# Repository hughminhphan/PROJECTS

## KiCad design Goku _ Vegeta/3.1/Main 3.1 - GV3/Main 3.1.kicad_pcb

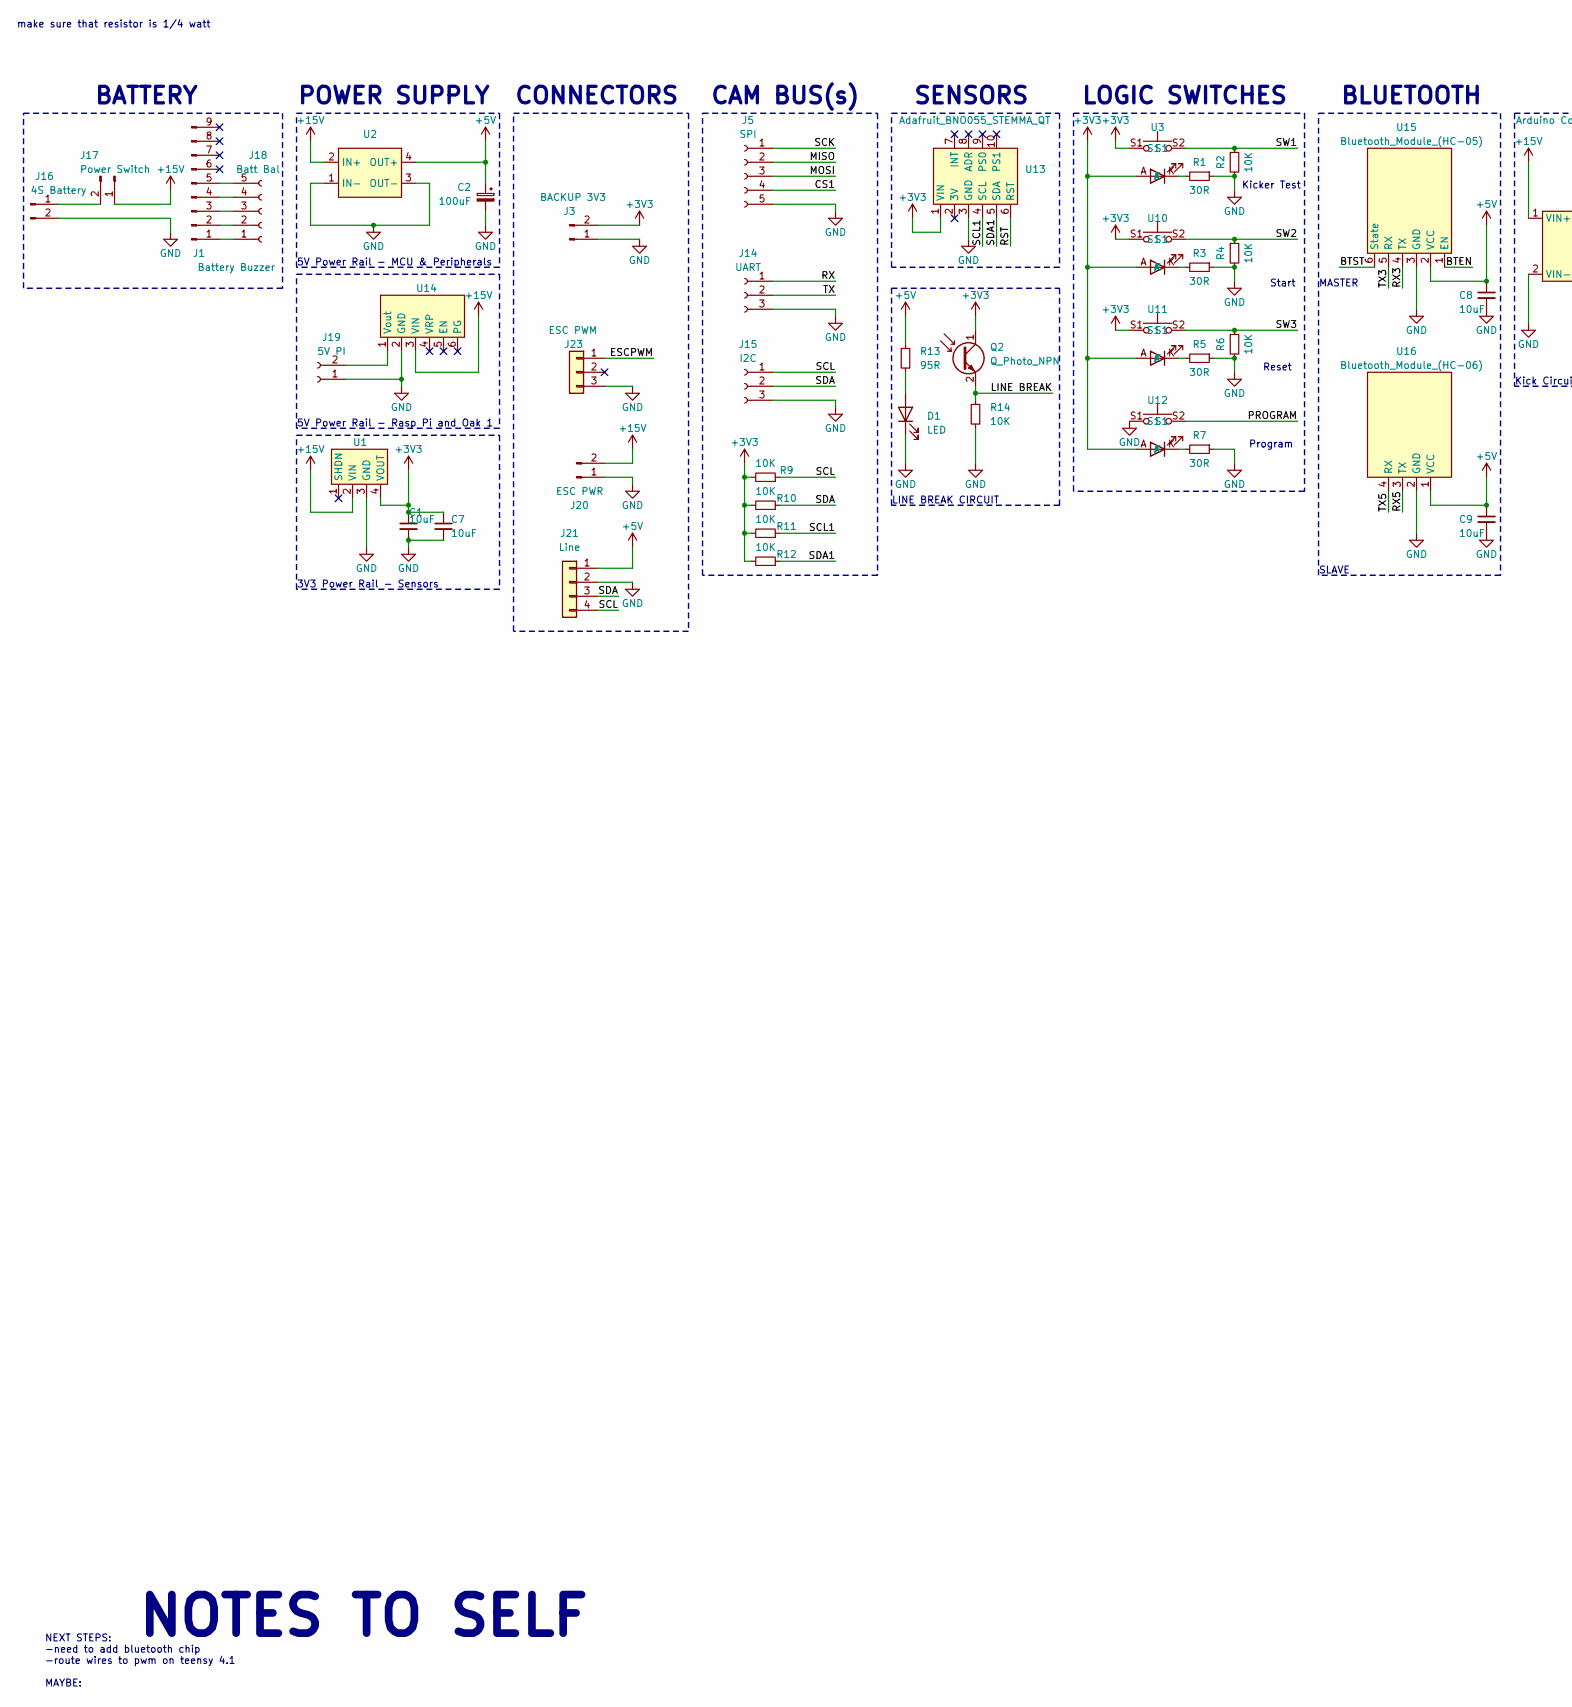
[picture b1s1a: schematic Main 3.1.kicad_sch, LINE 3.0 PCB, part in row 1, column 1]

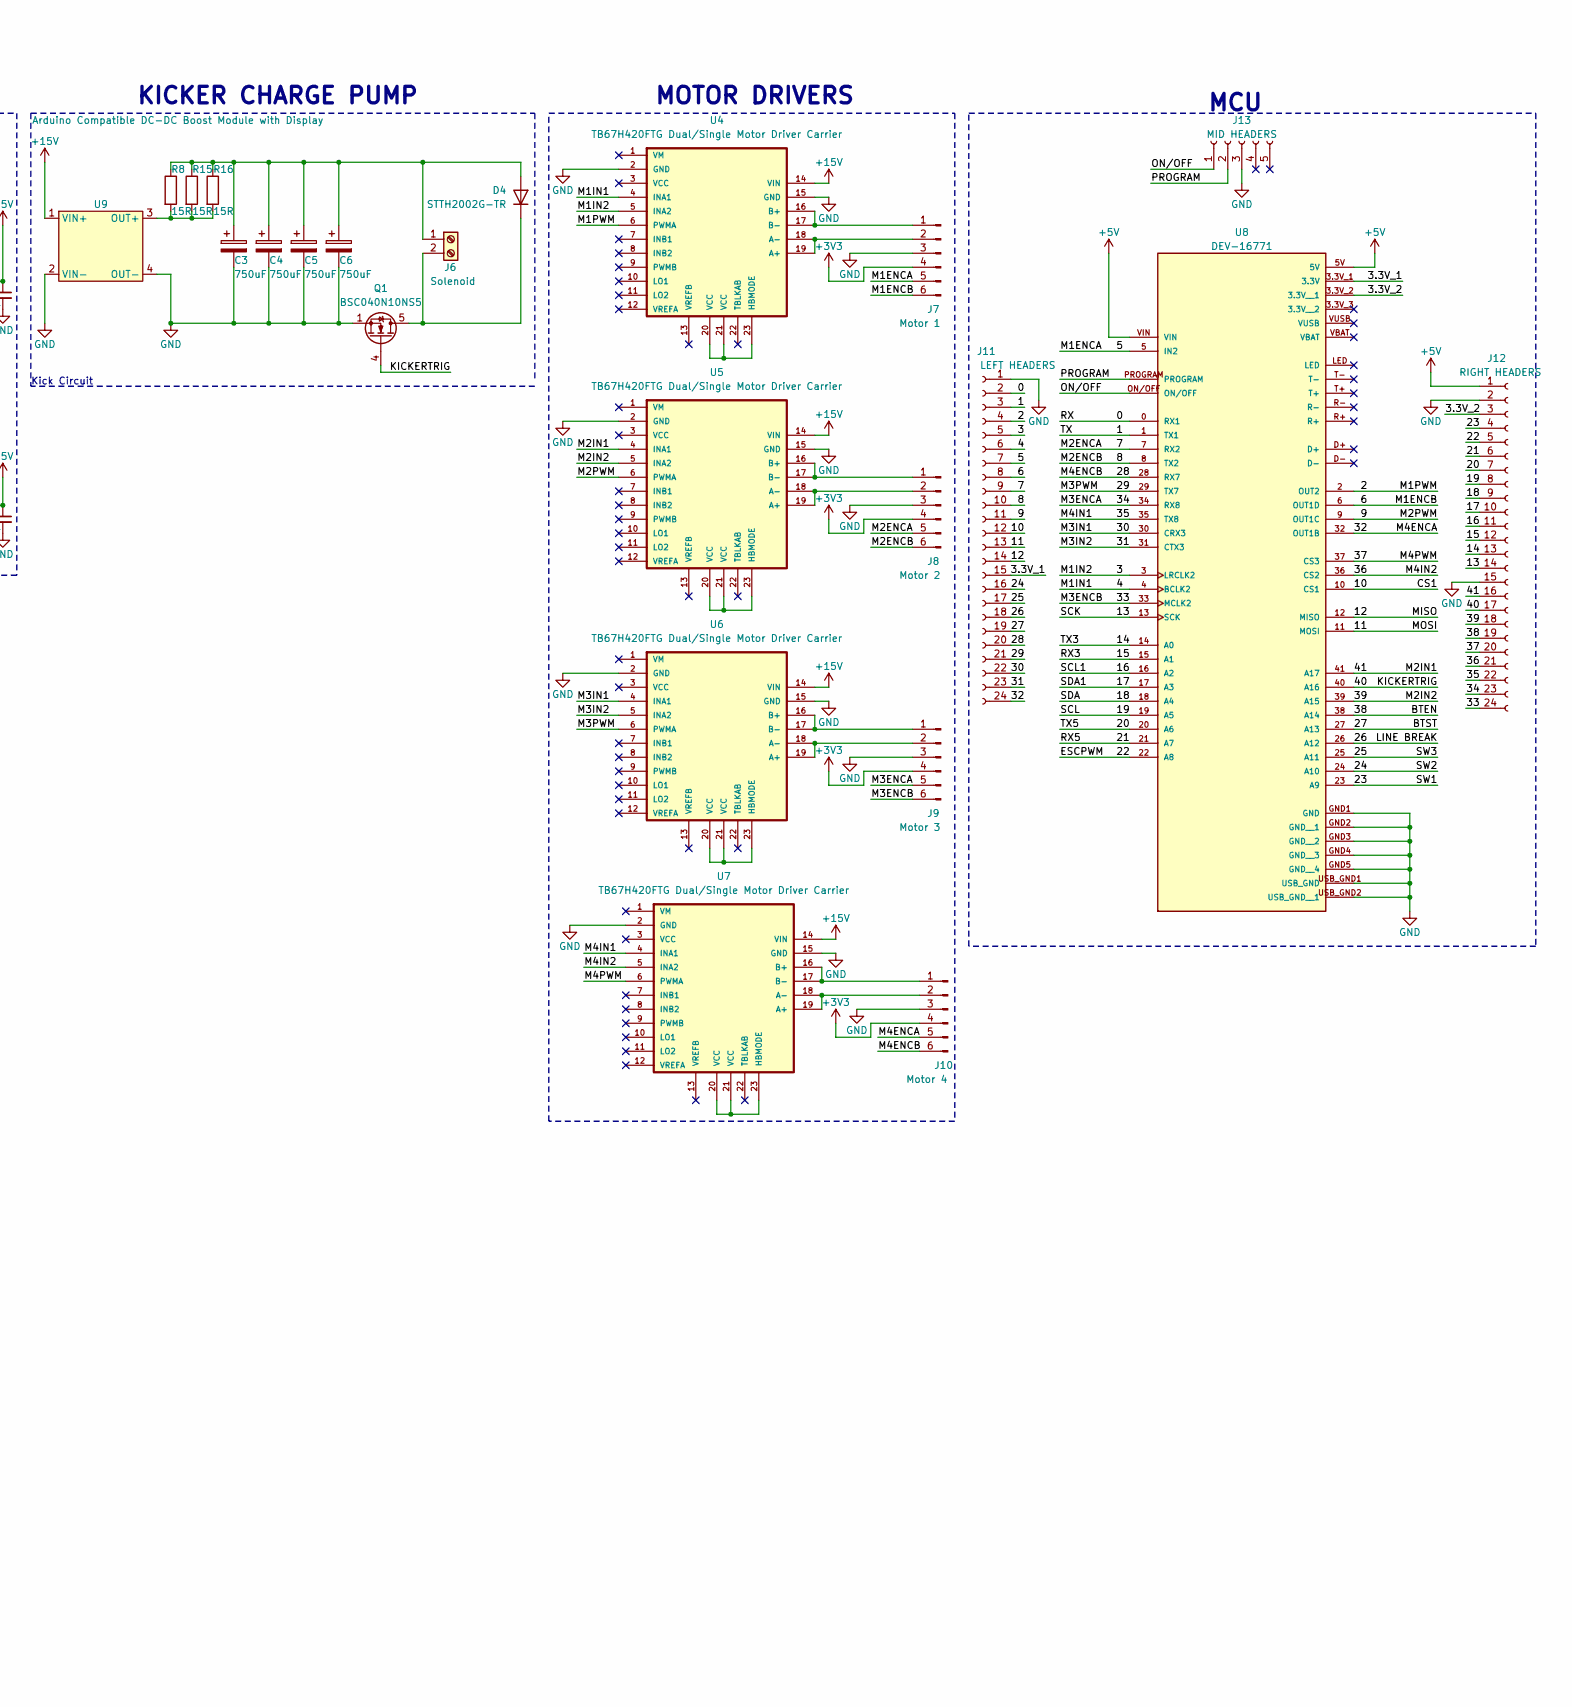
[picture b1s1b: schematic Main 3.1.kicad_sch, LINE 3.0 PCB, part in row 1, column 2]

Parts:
C1, C7, C8, C9: 10uF; C_0805_2012Metric
C2: 100uF; CP_Radial_D10.0mm_P5.00mm
C3, C4, C5, C6: 750uF; CP_Radial_D10.0mm_P5.00mm
D1: LED; LED_D3.0mm
D4: STTH2002G-TR; TO-263-2
J1: Battery Buzzer; PinHeader_1x09_P2.54mm_Vertical
J3: BACKUP 3V3; SolderWire-0.75sqmm_1x02_P4.8mm_D1.25mm_OD2.3mm
J5: SPI; PinSocket_1x05_P2.54mm_Vertical
J6: Solenoid; SolderWire-0.75sqmm_1x02_P4.8mm_D1.25mm_OD2.3mm
J7: Motor 1; PinSocket_1x06_P2.54mm_Vertical
J8: Motor 2; PinSocket_1x06_P2.54mm_Vertical
J9: Motor 3; PinSocket_1x06_P2.54mm_Vertical
J10: Motor 4; PinSocket_1x06_P2.54mm_Vertical
J11: LEFT HEADERS; PinHeader_1x24_P2.54mm_Vertical
J12: RIGHT HEADERS; PinHeader_1x24_P2.54mm_Vertical
J13: MID HEADERS; PinHeader_1x05_P2.54mm_Vertical
J14: UART; PinSocket_1x03_P2.54mm_Vertical
J15: I2C; PinSocket_1x03_P2.54mm_Vertical
J16: 4S Battery; DEANS
J17: Power Switch; AMASS_XT30UPB-F_1x02_P5.0mm_Vertical
J18: Batt Bal; JST_XH_B5B-XH-A_1x05_P2.50mm_Vertical
J19: 5V PI; SolderWire-0.75sqmm_1x02_P4.8mm_D1.25mm_OD2.3mm
J20: ESC PWR; SolderWire-0.5sqmm_1x02_P4.6mm_D0.9mm_OD2.1mm
J21: Line; JST_XH_B4B-XH-A_1x04_P2.50mm_Vertical
J23: ESC PWM; PinHeader_1x03_P2.54mm_Vertical
Q1: BSC040N10NS5; TDSON-8-1
Q2: Q_Photo_NPN; LED_D3.0mm
R1, R3, R5, R7: 30R; R_0805_2012Metric
R2, R4, R6, R9, R10, R11, R12, R14: 10K; R_0805_2012Metric
R8, R15, R16: 15R; R_Axial_DIN0207_L6.3mm_D2.5mm_P10.16mm_Horizontal
R13: 95R; R_0805_2012Metric
U1: Pololu 3.3V, 500mA Step-Down Voltage Regulator D24V5F3
U2: DC-DC Multi-output Buck Converter
U3, U10, U11, U12: SW_Cherry_MX_3mmLED
U4, U5, U6, U7: TB67H420FTG Dual/Single Motor Driver Carrier; TB67H420FTG DualSingle Motor Driver Carrier
U8: DEV-16771; MODULE_DEV-16771; PARTREV 4.1
U9: Arduino Compatible DC-DC Boost Module with Display
U13: Adafruit_BNO055_STEMMA_QT; Adafruit IMU BNO055
U14: 5V, 5.5A Step-Down Voltage Regulator D36V50F5
U15: Bluetooth_Module_(HC-05); PinHeader_1x06_P2.54mm_Vertical
U16: Bluetooth_Module_(HC-06); PinHeader_1x04_P2.54mm_Vertical

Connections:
+3V3: C1.1, C7.1, J3.2, J7.4, J8.4, J9.4, J10.4, Q2.1 (C), R9.2, R10.2, R11.2, R12.2, U1.4 (VOUT), U3.A, U3.S1, U10.A, U10.S1, U11.A, U11.S1, U12.A, U13.1 (VIN)
+5V: C2.1, C8.1, C9.1, J12.1, J21.1, R13.1, U2.4 (OUT+), U8.5V, U8.VIN, U15.2 (VCC), U16.1 (VCC)
+15V: J17.1, J20.2, U1.2 (VIN), U2.2 (IN+), U4.14 (VIN), U5.14 (VIN), U6.14 (VIN), U7.14 (VIN), U9.1 (VIN+), U14.3 (VIN)
/0: J11.2, J14.1, U8.0 (RX1)
/1: J11.3, J14.2, U8.1 (TX1)
/2: J11.4, U4.6 (PWMA), U8.2 (OUT2)
/3: J11.5, U4.5 (INA2), U8.3 (LRCLK2)
/3.3V_1: J11.15, U8.3.3V_1 (3.3V)
/3.3V_2: J12.3, U8.3.3V_2 (3.3V__1)
/4: J11.6, U4.4 (INA1), U8.4 (BCLK2)
/5: J7.5, J11.7, U8.5 (IN2)
/6: J7.6, J11.8, U8.6 (OUT1D)
/7: J8.5, J11.9, U8.7 (RX2)
/8: J8.6, J11.10, U8.8 (TX2)
/9: J11.11, U5.6 (PWMA), U8.9 (OUT1C)
/10: J5.4, J11.12, U8.10 (CS1)
/11: J5.3, J11.13, U8.11 (MOSI)
/12: J5.2, J11.14, U8.12 (MISO)
/13: J5.1, J12.14, U8.13 (SCK)
/14: J12.13, U8.14 (A0), U15.5 (RX)
/15: J12.12, U8.15 (A1), U15.4 (TX)
/16: J12.11, R11.1, U8.16 (A2), U13.4 (SCL)
/17: J12.10, R12.1, U8.17 (A3), U13.5 (SDA)
/18: J12.9, J15.2, J21.3, R10.1, U8.18 (A4)
/19: J12.8, J15.1, J21.4, R9.1, U8.19 (A5)
/20: J12.7, U8.20 (A6), U16.4 (RX)
/21: J12.6, U8.21 (A7), U16.3 (TX)
/22: J12.5, J23.1, U8.22 (A8)
/23: J12.4, R2.1, U3.S2 (S1), U8.23 (A9)
/24: J11.16, R4.1, U8.24 (A10), U10.S2 (S1)
/25: J11.17, R6.1, U8.25 (A11), U11.S2 (S1)
/26: J11.18, Q2.2 (E), R14.1, U8.26 (A12)
/27: J11.19, U8.27 (A13), U15.6 (State)
/28: J10.6, J11.20, U8.28 (RX7)
/29: J11.21, U6.6 (PWMA), U8.29 (TX7)
/30: J11.22, U6.4 (INA1), U8.30 (CRX3)
/31: J11.23, U6.5 (INA2), U8.31 (CTX3)
/32: J10.5, J11.24, U8.32 (OUT1B)
/33: J9.6, J12.24, U8.33 (MCLK2)
/34: J9.5, J12.23, U8.34 (RX8)
/35: J12.22, U7.4 (INA1), U8.35 (TX8)
/36: J12.21, U7.5 (INA2), U8.36 (CS2)
/37: J12.20, U7.6 (PWMA), U8.37 (CS3)
/38: J12.19, U8.38 (A14), U15.1 (EN)
/39: J12.18, U5.5 (INA2), U8.39 (A15)
/40: J12.17, Q1.4 (G), U8.40 (A16)
/41: J12.16, U5.4 (INA1), U8.41 (A17)
/ON/OFF: J13.1, U8.ON/OFF
/PROGRAM: J13.2, U8.PROGRAM, U12.S2 (S1)
/RST: U13.6 (RST)
GND: C1.2, C2.2, C3.2, C4.2, C5.2, C6.2, C7.2, C8.2, C9.2, D1.1 (K), J3.1, J5.5, J7.3, J8.3, J9.3, J10.3, J11.1, J12.2, J12.15, J13.3, J14.3, J15.3, J16.2, J19.1, J20.1, J21.2, J23.3, Q1.1 (S), Q1.2 (S), Q1.3 (S), R1.1, R2.2, R3.1, R4.2, R5.1, R6.2, R7.1, R14.2, U1.3 (GND), U2.1 (IN-), U2.3 (OUT-), U4.2 (GND), U4.15 (GND), U5.2 (GND), U5.15 (GND), U6.2 (GND), U6.15 (GND), U7.2 (GND), U7.15 (GND), U8.GND1 (GND), U8.GND2 (GND__1), U8.GND3 (GND__2), U8.GND4 (GND__3), U8.GND5 (GND__4), U8.USB_GND1 (USB_GND), U8.USB_GND2 (USB_GND__1), U9.2 (VIN-), U9.4 (OUT-), U12.S1, U13.3 (GND), U14.2 (GND), U15.3 (GND), U16.2 (GND)
unnamed: D1.2 (A), R13.2
unnamed: C3.1, C4.1, C5.1, C6.1, D4.3 (A), J6.1, R8.1, R15.1, R16.1
unnamed: D4.2 (K), J6.2, Q1.5 (D)
unnamed: J1.1, J18.1
unnamed: J1.2, J18.2
unnamed: J1.3, J18.3
unnamed: J1.4, J18.4
unnamed: J1.5, J18.5
unnamed: J7.1, U4.16 (B+), U4.17 (B-)
unnamed: J7.2, U4.18 (A-), U4.19 (A+)
unnamed: J8.1, U5.16 (B+), U5.17 (B-)
unnamed: J8.2, U5.18 (A-), U5.19 (A+)
unnamed: J9.1, U6.16 (B+), U6.17 (B-)
unnamed: J9.2, U6.18 (A-), U6.19 (A+)
unnamed: J10.1, U7.16 (B+), U7.17 (B-)
unnamed: J10.2, U7.18 (A-), U7.19 (A+)
unnamed: J16.1, J17.2
unnamed: J19.2, U14.1 (Vout)
unnamed: R1.2, U3.K
unnamed: R3.2, U10.K
unnamed: R5.2, U11.K
unnamed: R7.2, U12.K
unnamed: U4.20 (VCC), U4.21 (VCC), U4.23 (HBMODE)
unnamed: U5.20 (VCC), U5.21 (VCC), U5.23 (HBMODE)
unnamed: U6.20 (VCC), U6.21 (VCC), U6.23 (HBMODE)
unnamed: U7.20 (VCC), U7.21 (VCC), U7.23 (HBMODE)
unnamed: R8.2, R15.2, R16.2, U9.3 (OUT+)

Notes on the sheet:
Program
NOTES TO SELF
NEXT STEPS: -need to add bluetooth chip -route wires to pwm on teensy 4.1 MAYBE:
Kicker Test
CONNECTORS
BATTERY
SLAVE
POWER SUPPLY
SENSORS
make sure that resistor is 1/4 watt
LINE BREAK CIRCUIT
5V Power Rail - Rasp Pi and Oak 1
MASTER
Start
Reset
Kick Circuit
LOGIC SWITCHES
BLUETOOTH
MCU
KICKER CHARGE PUMP
5V Power Rail - MCU & Peripherals
CAM BUS(s)
3V3 Power Rail - Sensors
MOTOR DRIVERS

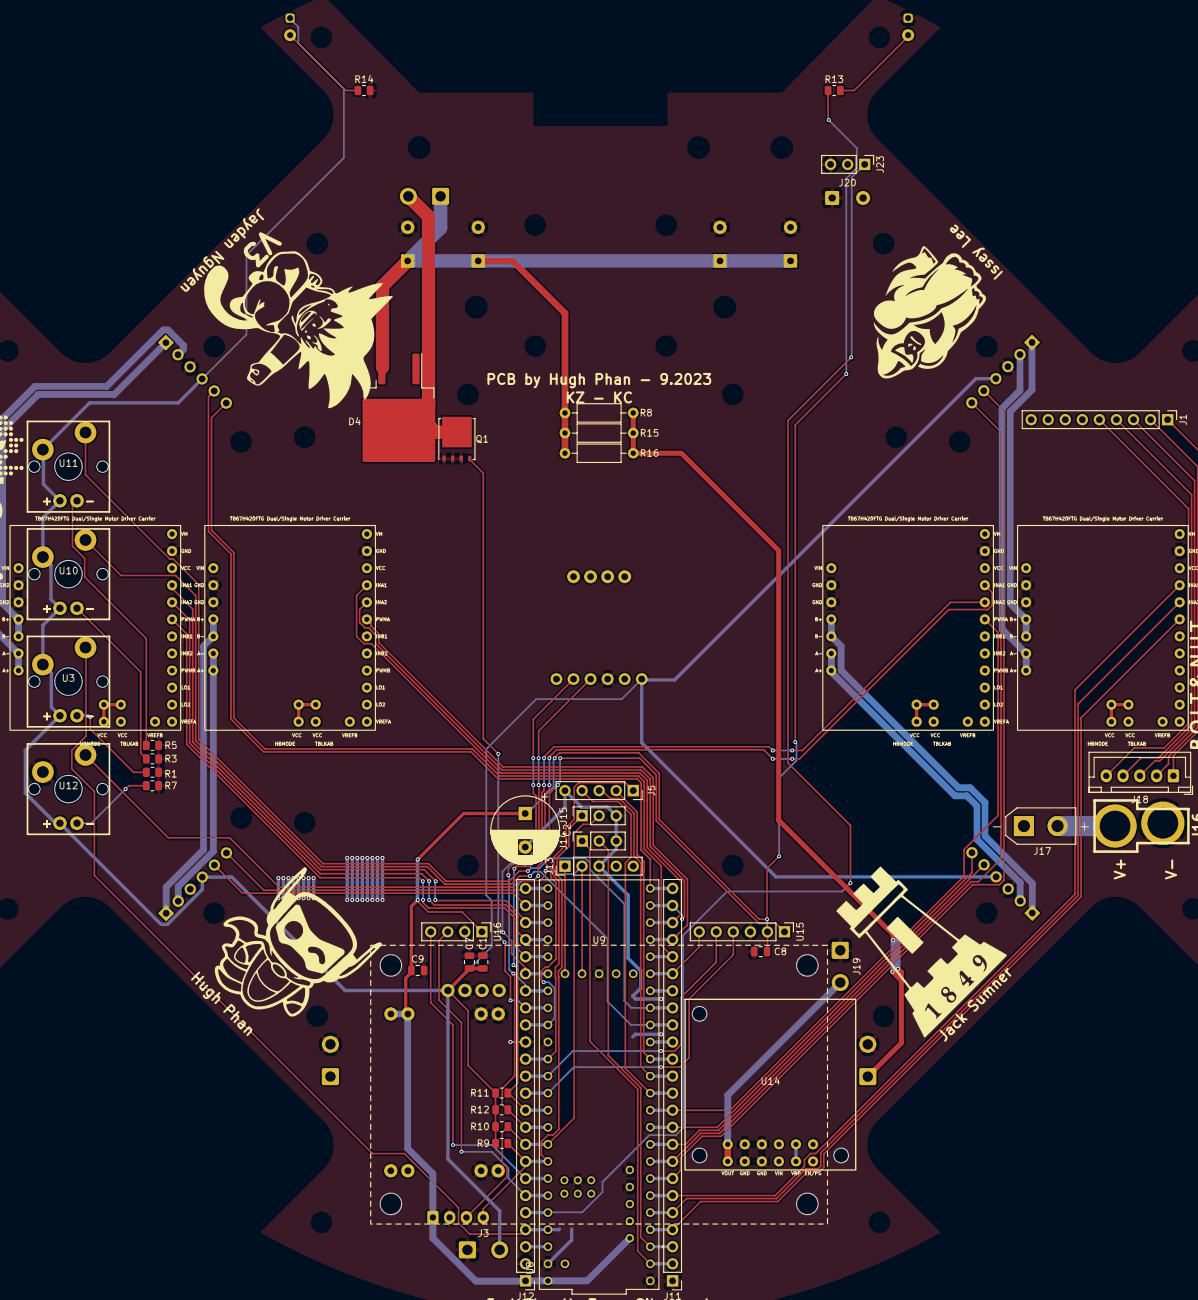
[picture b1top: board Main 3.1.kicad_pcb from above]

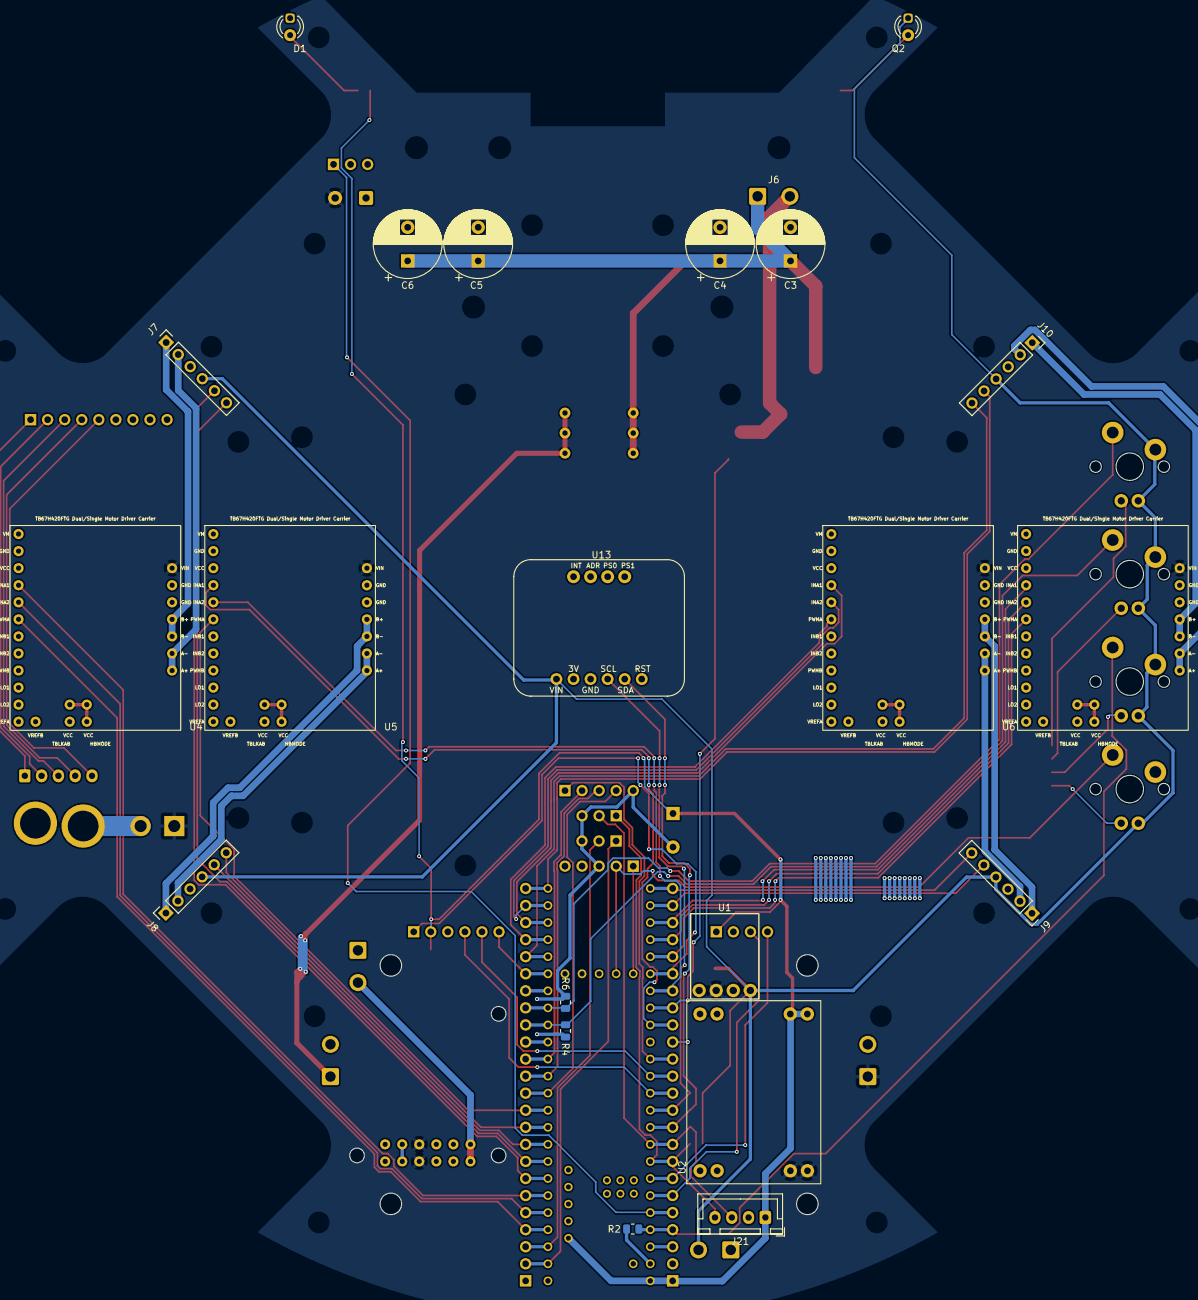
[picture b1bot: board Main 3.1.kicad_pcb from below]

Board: 2 copper layers, 65 parts (22 on the bottom side), 77 nets.

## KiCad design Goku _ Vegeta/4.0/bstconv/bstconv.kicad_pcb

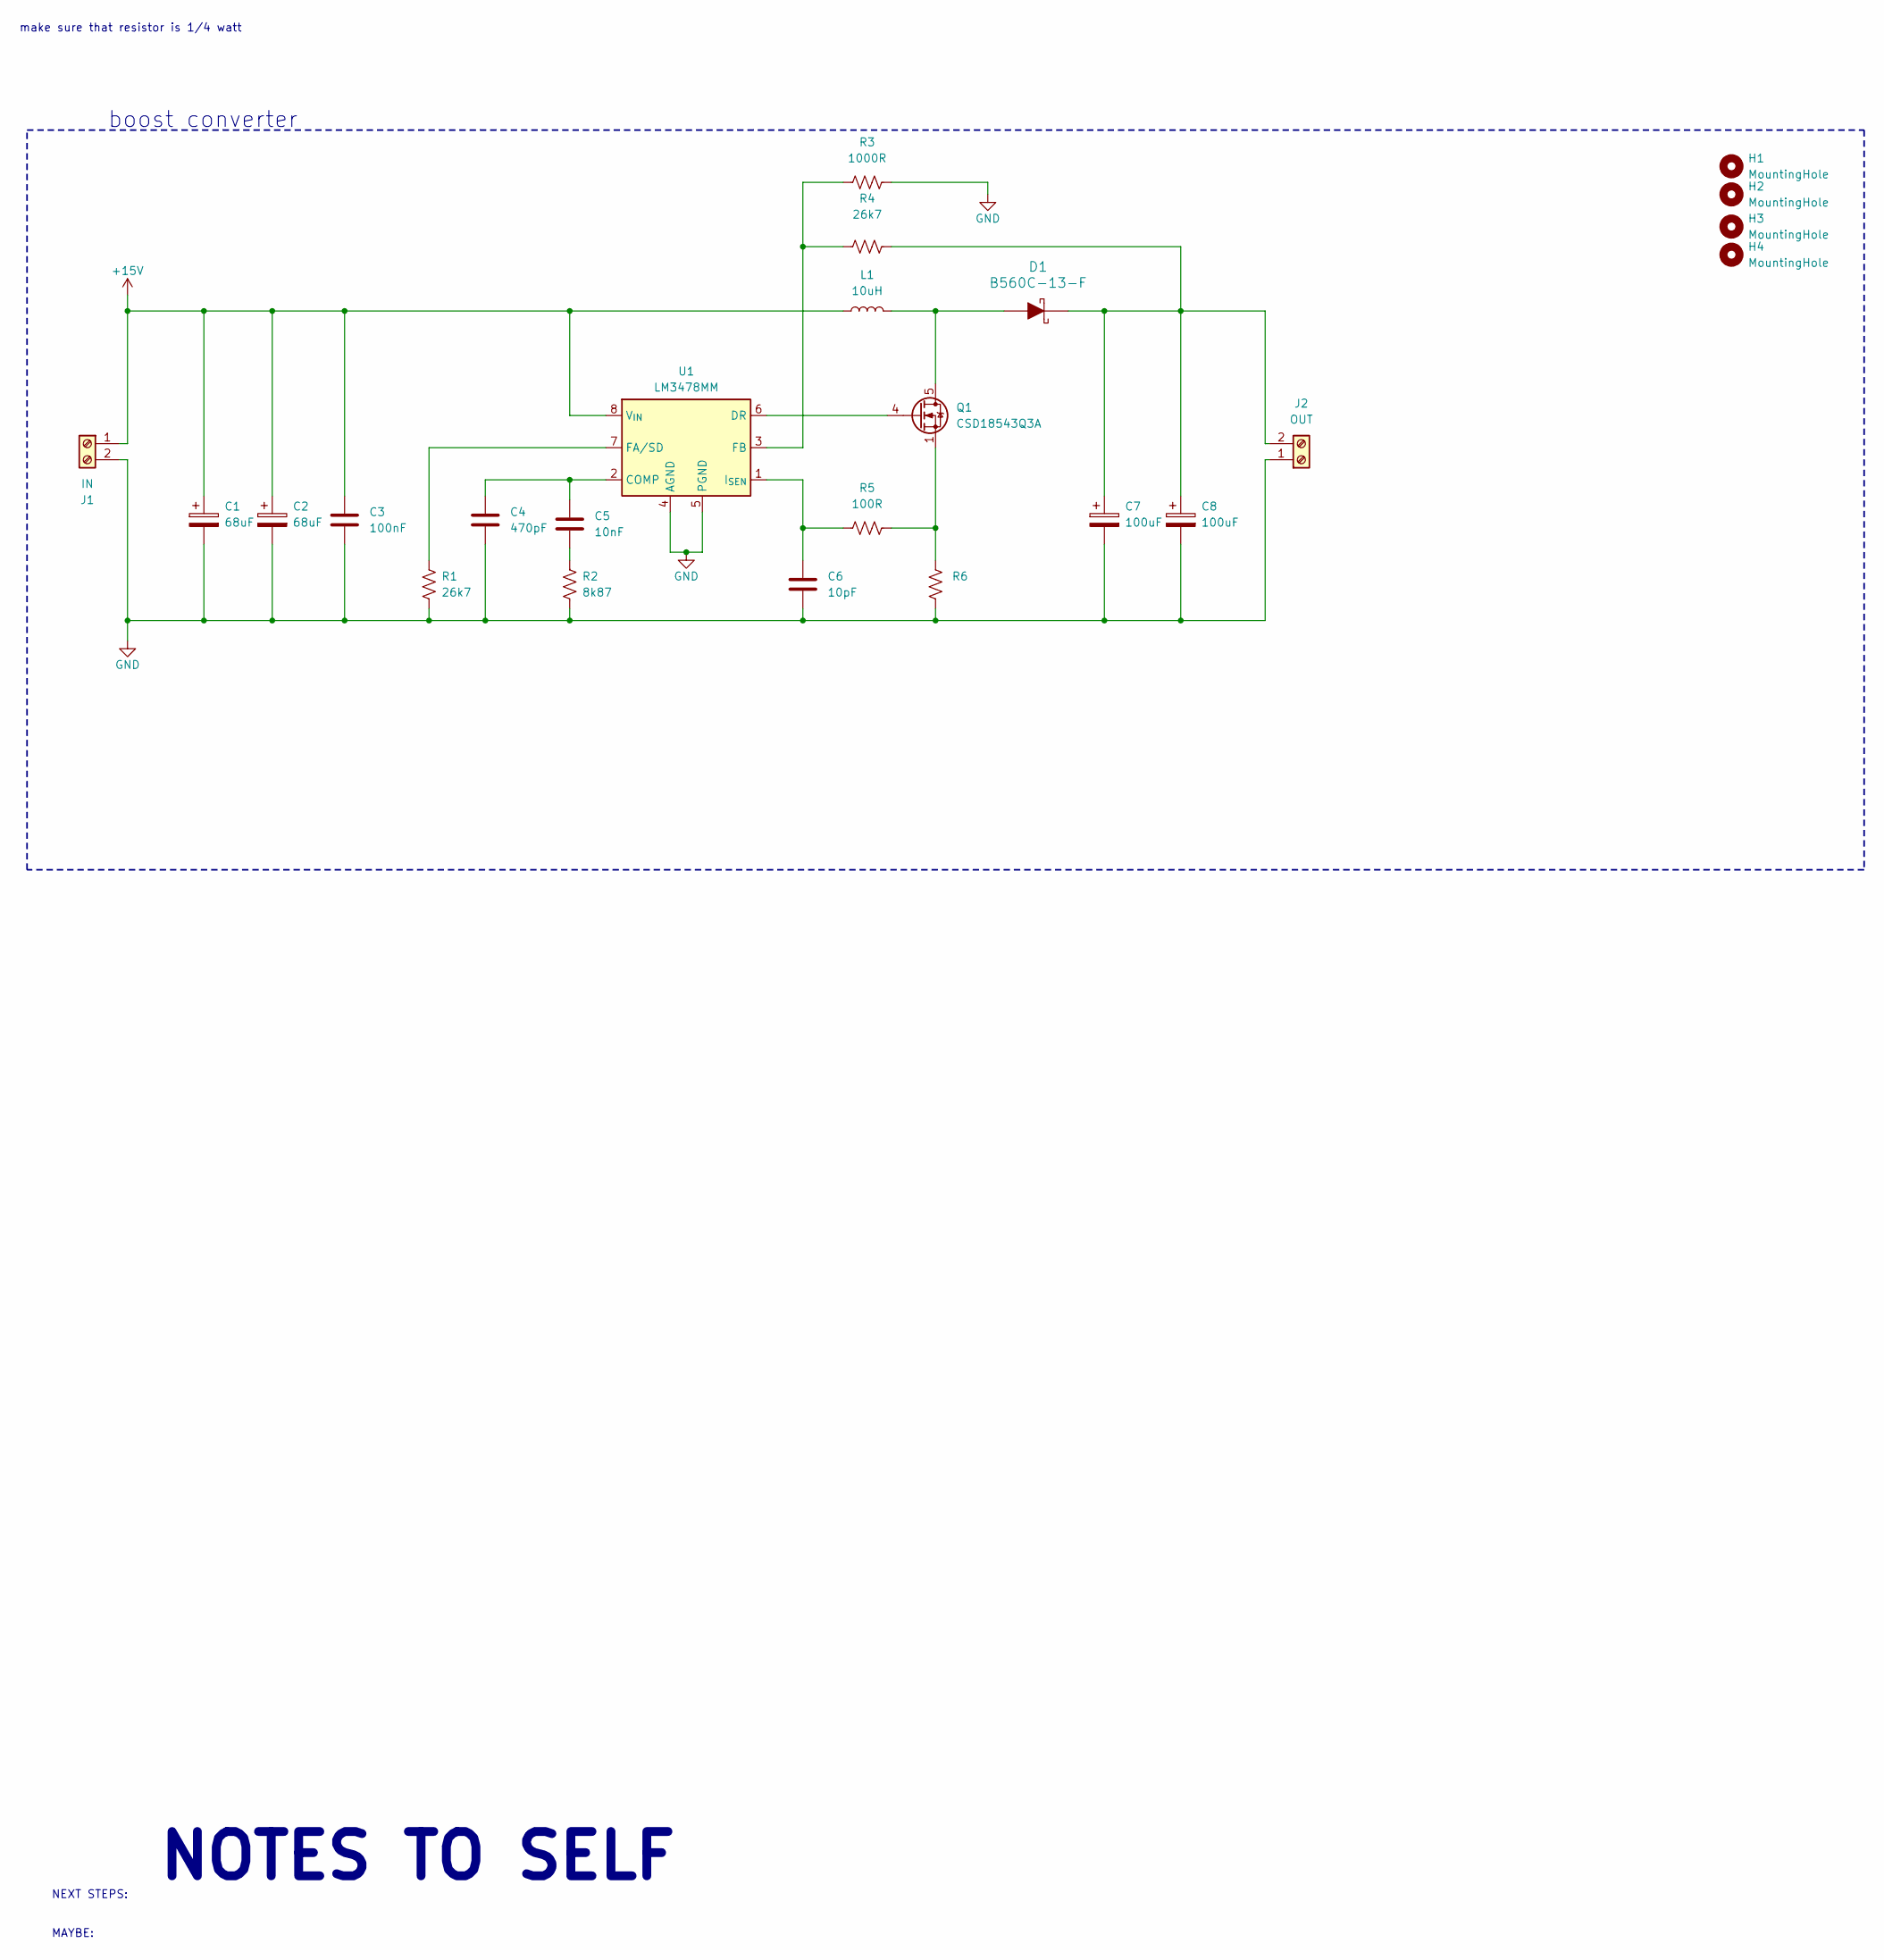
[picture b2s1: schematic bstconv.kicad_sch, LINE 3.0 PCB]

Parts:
C1, C2: 68uF; CP_Elec_6.3x7.7
C3: 100nF; C_0805_2012Metric
C4: 470pF; C_0805_2012Metric
C5: 10nF; C_0402_1005Metric
C6: 10pF; C_0805_2012Metric
C7, C8: 100uF; CP_Elec_10x10.5
D1: B560C-13-F; DO-214AB; MPN B560C-13-F; Digi-Key_PN B560C-FDICT-ND
H1, H2, H3, H4: MountingHole; MountingHole_3.2mm_M3
J1: IN; TerminalBlock_Phoenix_MKDS-1,5-2-5.08_1x02_P5.08mm_Horizont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
J2: OUT; TerminalBlock_Phoenix_MKDS-1,5-2-5.08_1x02_P5.08mm_Horizont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
L1: 10uH; L_12x12mm_H8mm
Q1: CSD18543Q3A; VSON-8_3.3x3.3mm_P0.65mm_NexFET
R1, R4: 26k7; R_0402_1005Metric
R2: 8k87; R_0402_1005Metric
R3: 1000R; R_0402_1005Metric
R5: 100R; R_0402_1005Metric
R6: 8mR; R_0612_1632Metric
U1: LM3478MM; VSSOP-8_3.0x3.0mm_P0.65mm

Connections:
+15V: C1.1, C2.1, C3.1, J1.1, L1.1, U1.8 (V_{IN})
GND: C1.2, C2.2, C3.2, C4.2, C6.2, C7.2, C8.2, J1.2, J2.1, R1.2, R2.2, R3.2, R6.1, U1.4 (AGND), U1.5 (PGND)
unnamed: C5.2, R2.1
unnamed: C7.1, C8.1, D1.K, J2.2, R4.2
unnamed: D1.A, L1.2, Q1.5 (D)
unnamed: Q1.4 (G), U1.6 (DR)
unnamed: Q1.1 (S), Q1.2 (S), Q1.3 (S), R5.2, R6.2
unnamed: C4.1, C5.1, U1.2 (COMP)
unnamed: R1.1, U1.7 (FA/SD)
unnamed: R3.1, R4.1, U1.3 (FB)
unnamed: C6.1, R5.1, U1.1 (I_{SEN})

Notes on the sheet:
NOTES TO SELF
NEXT STEPS: MAYBE:
boost converter
make sure that resistor is 1/4 watt

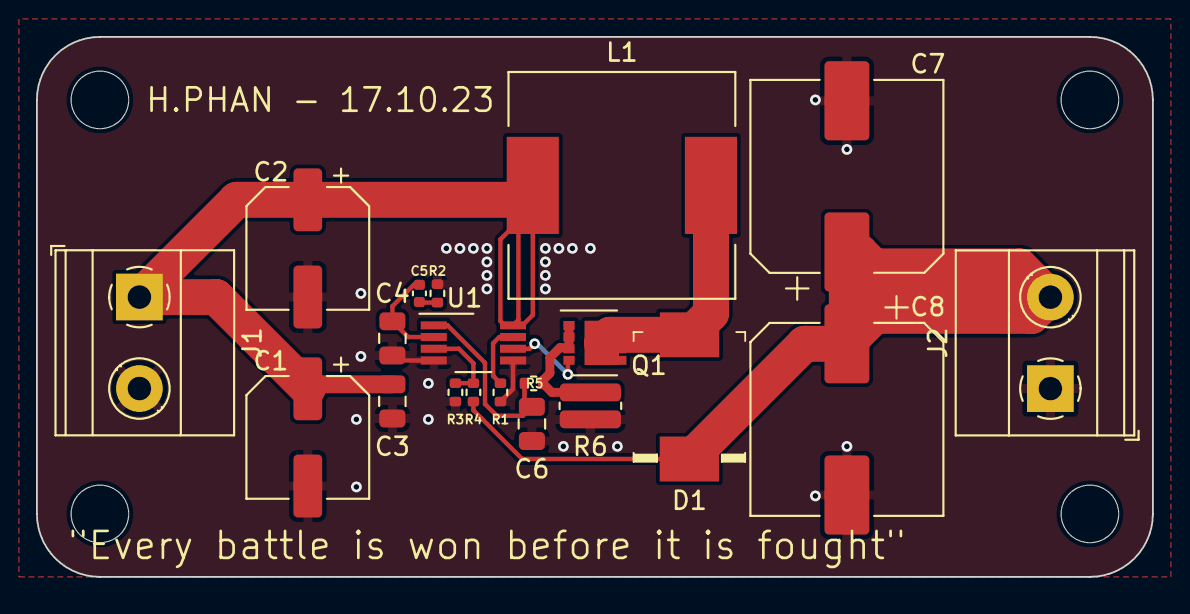
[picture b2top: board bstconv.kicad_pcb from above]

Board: 2 copper layers, 62.0 x 30.0 mm, 24 parts (0 on the bottom side), 11 nets.

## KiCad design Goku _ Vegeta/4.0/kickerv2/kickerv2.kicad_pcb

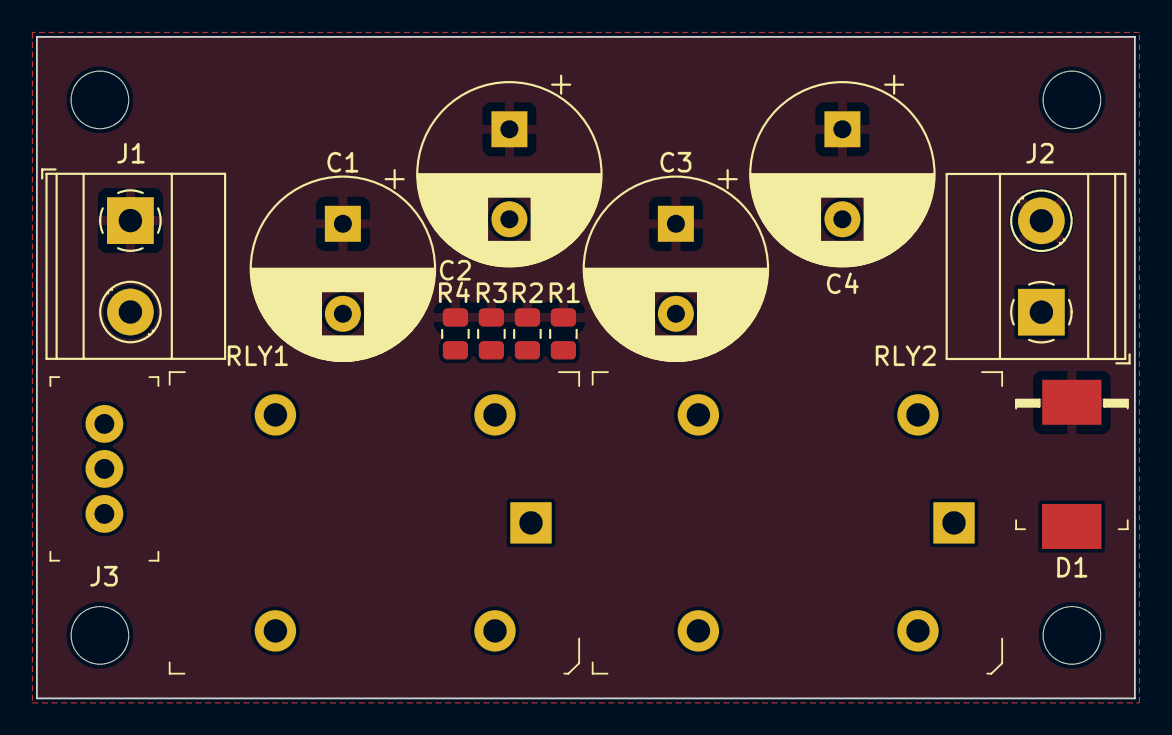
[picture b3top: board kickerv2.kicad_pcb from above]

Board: 2 copper layers, 61.0 x 36.8 mm, 18 parts (0 on the bottom side), 7 nets, no tracks yet.

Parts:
C1, C2, C3, C4: 1000uF; CP_Radial_D10.0mm_P5.00mm
D1: B560C-13-F; DO-214AB
H1, H2, H3, H4: MountingHole; MountingHole_3.2mm_M3
J1: IN; TerminalBlock_Phoenix_MKDS-1,5-2-5.08_1x02_P5.08mm_Horizont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
J2: OUT; TerminalBlock_Phoenix_MKDS-1,5-2-5.08_1x02_P5.08mm_Horizont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
J3: B3B-XH-A_LF__SN_; PinHeader_1x3_P2.5mm_Drill1.1mm
R1, R2, R3, R4: 12k; R_0805_2012Metric
RLY1, RLY2: G5LE-14_DC12; Relay_THT_G5LE-14

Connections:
+36V: C1.1, C2.1, C3.1, C4.1, D1.K, J1.1, J2.2, R1.1, R2.1, R3.1, R4.1
/CHARGE: J3.1, RLY1.5 (COIL)
/DISCHARGE: J3.2, RLY2.5 (COIL)
GND: J1.2, J3.3, RLY1.2 (COIL), RLY1.3 (NO), RLY2.2 (COIL)
unnamed: D1.A, J2.1, RLY2.1 (COM)
unnamed: C1.2, C2.2, C3.2, C4.2, RLY1.1 (COM), RLY2.3 (NO)
unnamed: R1.2, R2.2, R3.2, R4.2, RLY1.4 (NC)
